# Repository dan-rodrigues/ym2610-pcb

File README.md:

# YM2610 PCB

This project allows the user to control a YM2610(B) FM synthesis / ADPCM / SSG sound chip. Software is included to play back YM2610(B) VGM files which includes any Neo Geo arcade game and various others. It can also play certain Sega Genesis tracks using an included converter script. There is also a MIDI input that can be paired with new software to control the synth.

The goal is to make the complete system both low-cost and flexible which increases the complexity of the FPGA design but allows the use of cheaper hardware (i.e. a $35USD FPGA board and a fairly straightforward PCB).

The FPGA board used is the [iCEBreaker Bitsy](https://1bitsquared.com/collections/fpga/products/icebreaker-bitsy) which is also [open source](https://github.com/icebreaker-fpga/icebreaker). It's the small purple board in the bottom left of the photo. A custom vendor USB device and a companion host Python script is used for control. The USB core used is [no2usb](https://github.com/no2fpga/no2usb).

## Assembled PCBs

### v1.1.0 (partial)

### v1.0.1

## Video/Audio demos

* [Metal Slug 2 soundtrack](https://www.youtube.com/watch?v=nlexW8DgMvw) - Neo Geo VGM playback demo using S/PDIF audio output.
* [Thunder Force IV soundtrack](https://www.youtube.com/watch?v=O-OgxfgEnMU) - Sega Genesis playback demo using analog line-out output.

The Sega Genesis demos are made using an included converter script to compensate for incompatible hardware, different clock rates and differences in PCM playback.

## Features

### I/O

* S/PDIF compatible outputs. The digital sound sources from the OPNB (FM/PCM) can be heard using this output. The analog sound source (SSG) can only be heard with the 3.5mm analog outputs. Optical and coax outputs are included.
* 3.5mm line out.
* 3.5mm headphone out with attenutation pot.
* Separate attenuation pots for the combined FM/PCM and separate SSG sound sources. Their levels can be adjusted or muted independently.
* MIDI input (DIN-5). Default firmware includes library functions to read the MIDI messages into a minimal struct. There's also a simple FM demo.
* 2x user buttons. The default firmware uses them to cycle through the available sound sources.

The S/PDIF output is resampled to 48KHz and can be used to hear the original lossless output from the OPNB. It doesn't include the analog SSG output but most tracks don't use it.

The analog outputs include an active low pass filter (fC = approx 17KHz), independent attenutation pots for each sound source and can also be used to hear the analog SSG output.

### Debug

These aren't required but can be useful for debugging.

* UART header
* CRESET jumper
* CRESET button

## Operation

Included is also an SoC implementation for the FPGA (in the `rtl/` directory) and firmware that runs on this SoC (in the `fw/` directory). There's also a set of helper scripts to control the SoC over the USB port.

ADPCM samples are fetched from the FPGA board PSRAM. The host PCB itself doesn't include any extra memory, only some standard logic to mux the PCM buses to the limited number of FPGA IO available. The RAM is 64MBit which is smaller than the 128MBit address space of samples, but the player script relocates and remaps samples starting from address 0 if needed. This means tracks that use the 128MBit space will work assuming the total PCM size of the track is less than 64MBit, which it likely is.

Both the original YM3016 DAC and the FPGA have access to the digital outputs of the synth. This means both analog output (using the DAC) and digital output (using the coax/optical output) is available. S/PDIF encoding is done on the FPGA and made available from the digital outputs.

The synth has a pair of PCM buses that work in parallel and the board only includes a single RAM which must be shared. The slower of the two buses is automatically paused when the faster bus begins a read which handles the contention issue. Only 4 FPGA IOs are used to read the 26 PCM bus pins which is handled using standard logic on the board.

The iCEBreaker Bitsy USB port is used to upload music data and also for control. The USB stack used and firmware can be customised as needed i.e. to allow a PC MIDI interface to drive the OPNB, or to record the raw digital output to store on a file, or any other possible use.

There is only 128KByte of RAM available to the software which would limit the maximum size of track that can be played. The track commands are streamed over USB to get around this limit which means tracks can be arbitrarily large. A pair of 8KByte buffers are read/written to support playback of large tracks.

Synth commands are output using a pair of 8bit shift registers, running at the same 8MHz clock as the synth itself. This reduces the needed IO count without being a bottleneck.

## Usage

### Build and flash

This project uses submodules which must be cloned first.

```
git submodule update --init --recursive
```

Building and flashing FPGA bitstream (which implements the SoC):

```
make dfuprog
```

Building and flashing SoC firmware:

```
make -C fw dfuprog
```

### Playing VGM files

After flashing the firmware, the RGB LED should slowly flash indicating that it's ready to use. Either `vgz` or `vgm` files can be used.

```
./scripts/usb_ctrl.py track.vgm
```

More details about the scripts can be found in their [README](scripts/README.md) file.

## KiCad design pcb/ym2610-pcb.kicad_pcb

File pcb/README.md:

# PCB

Included is the schematic and PCB layout of the board.

## Usage

Most ICs on the board are optional but a few are required in any case:

* 2x 74AHCT595: Shift registers to control the YM2610(B) and reset both the 2610 and the 3016.
* 1x 74LV1T34: Clock buffer, also shifts the 8MHz clock from 3.3v to 5v.

If ADPCM-A/B playback is needed, then these are required:

* 4x 74HCT153
* 1x 74LVC257
* 1x 74LVC2G08
* 1x 74LVC244

The analog section is optional assuming the SSG sound source isn't needed. To listen to the digital sound sources using S/PDIF output, there are optional optical and coax outputs. The coax output does not use a pulse transformer and one can be added if needed. 

## License

CERL-OHL-S-2.0. There is a copy of the text included in the licenses/ directory in the root of this repo. License text can also be found [here](https://ohwr.org/cern_ohl_s_v2.txt).

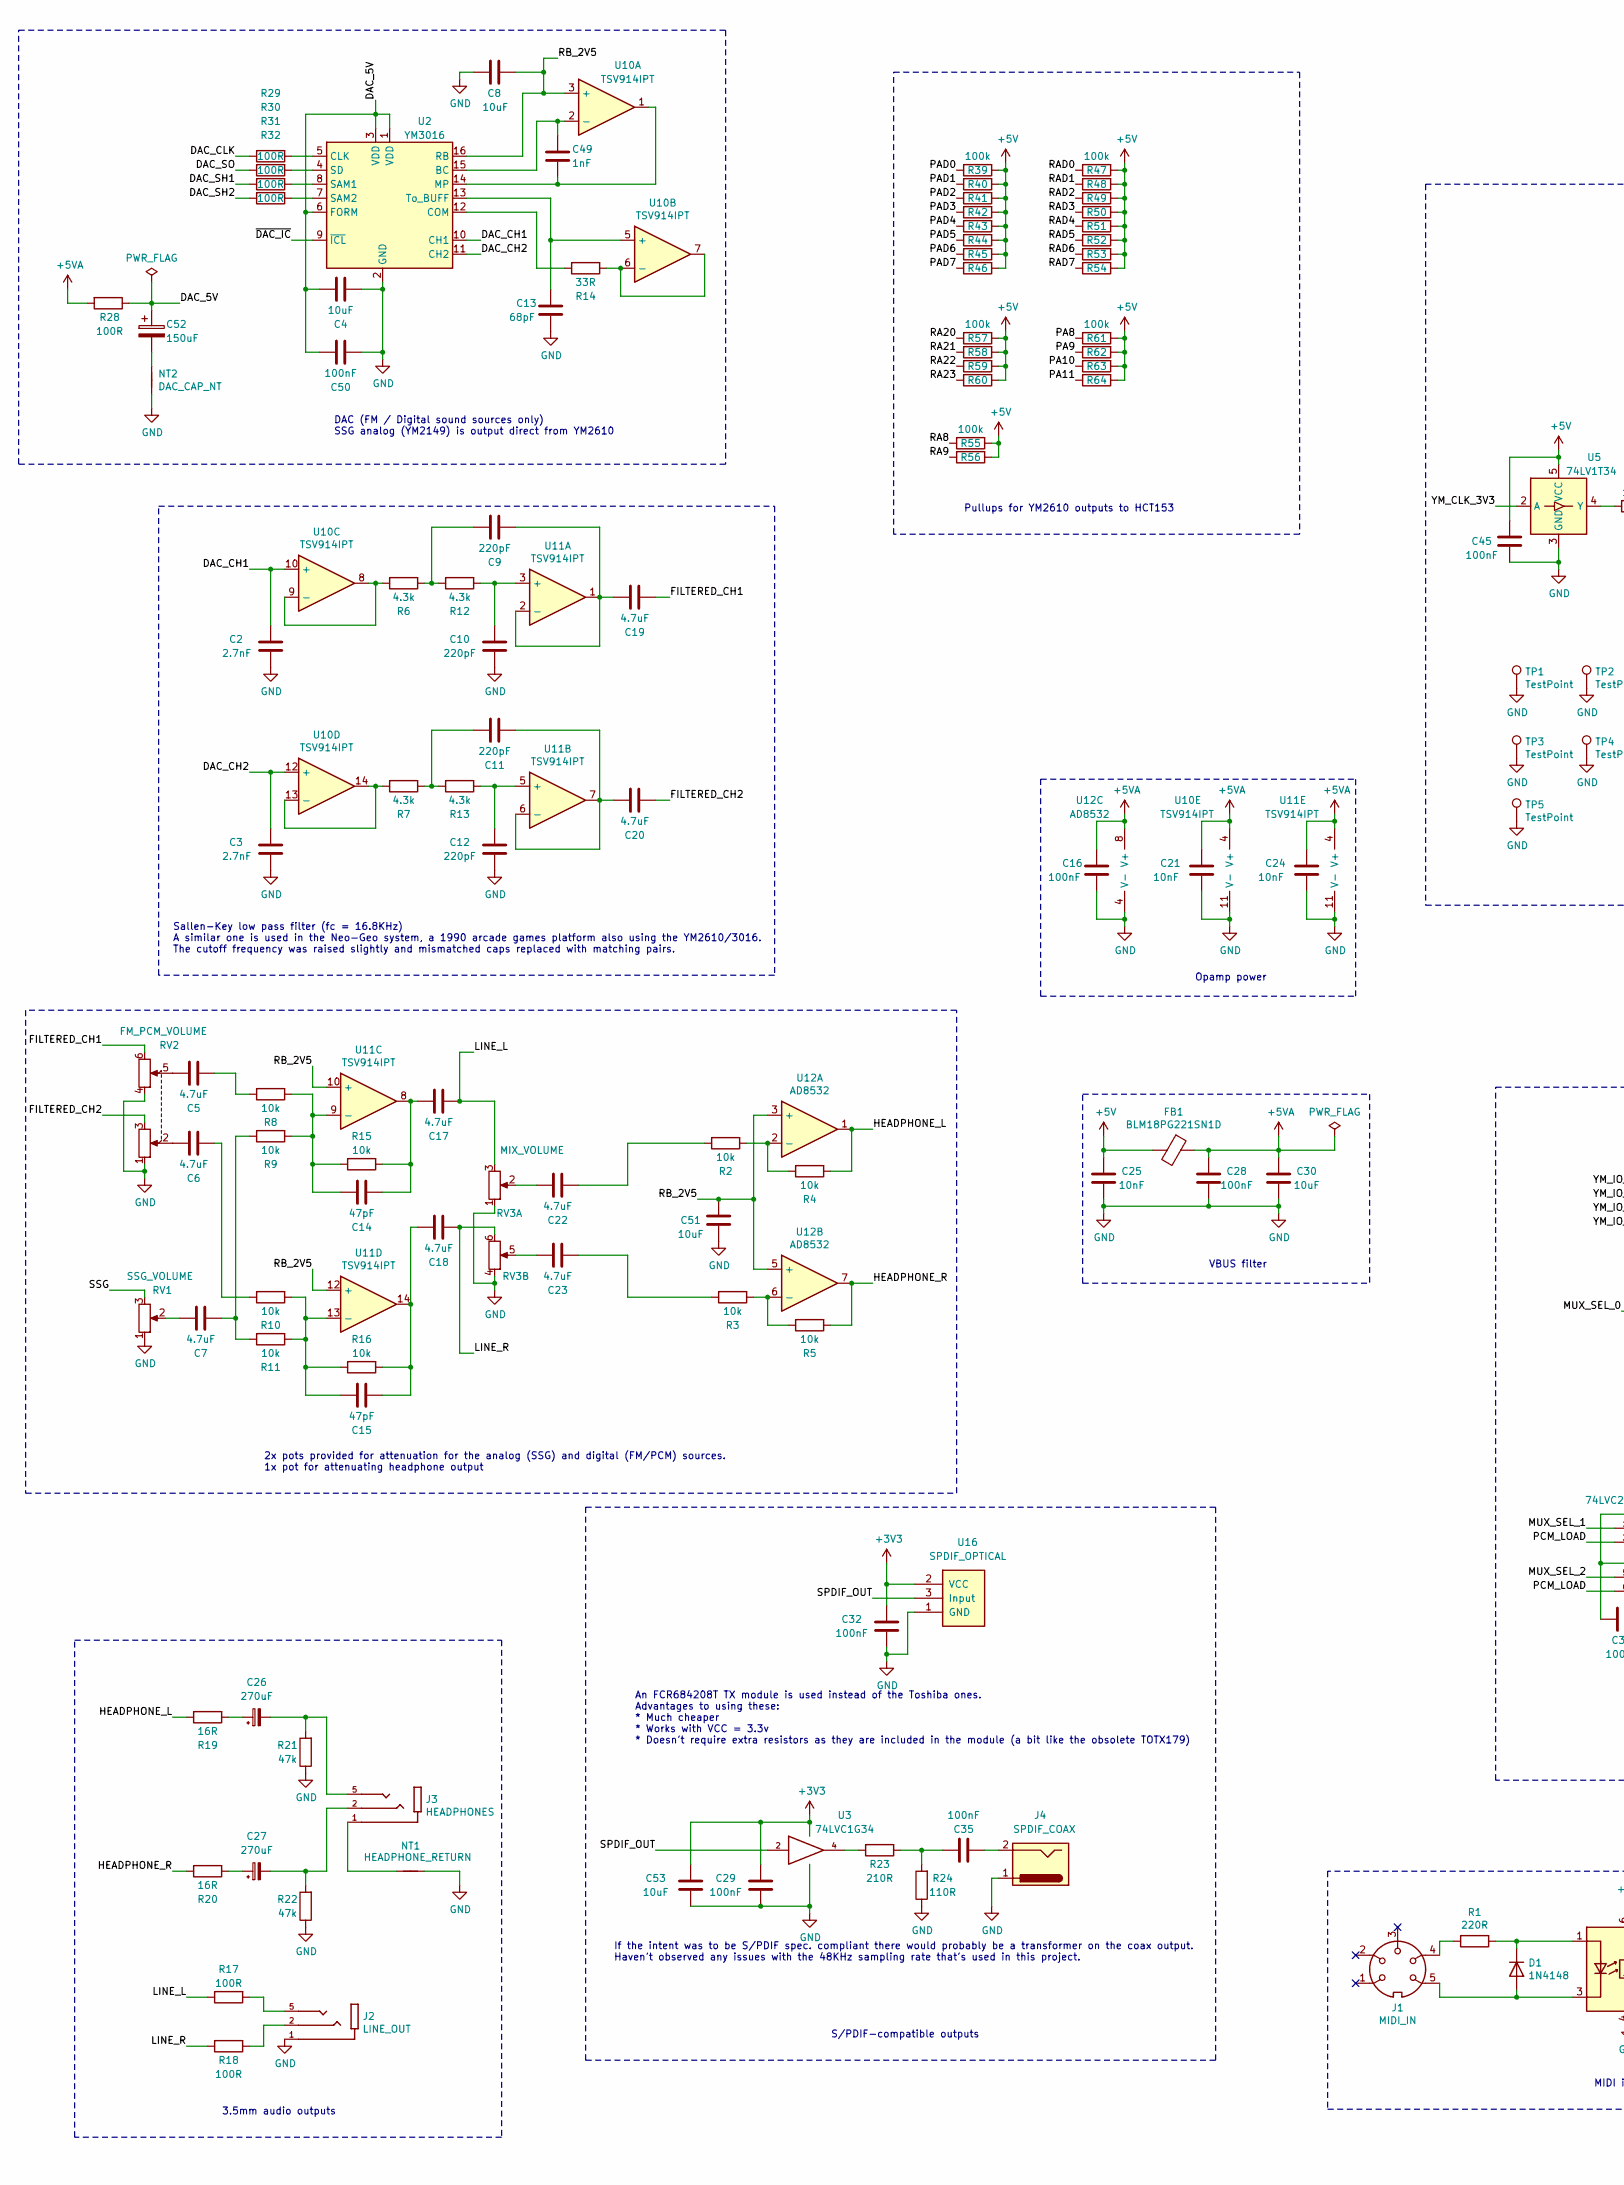
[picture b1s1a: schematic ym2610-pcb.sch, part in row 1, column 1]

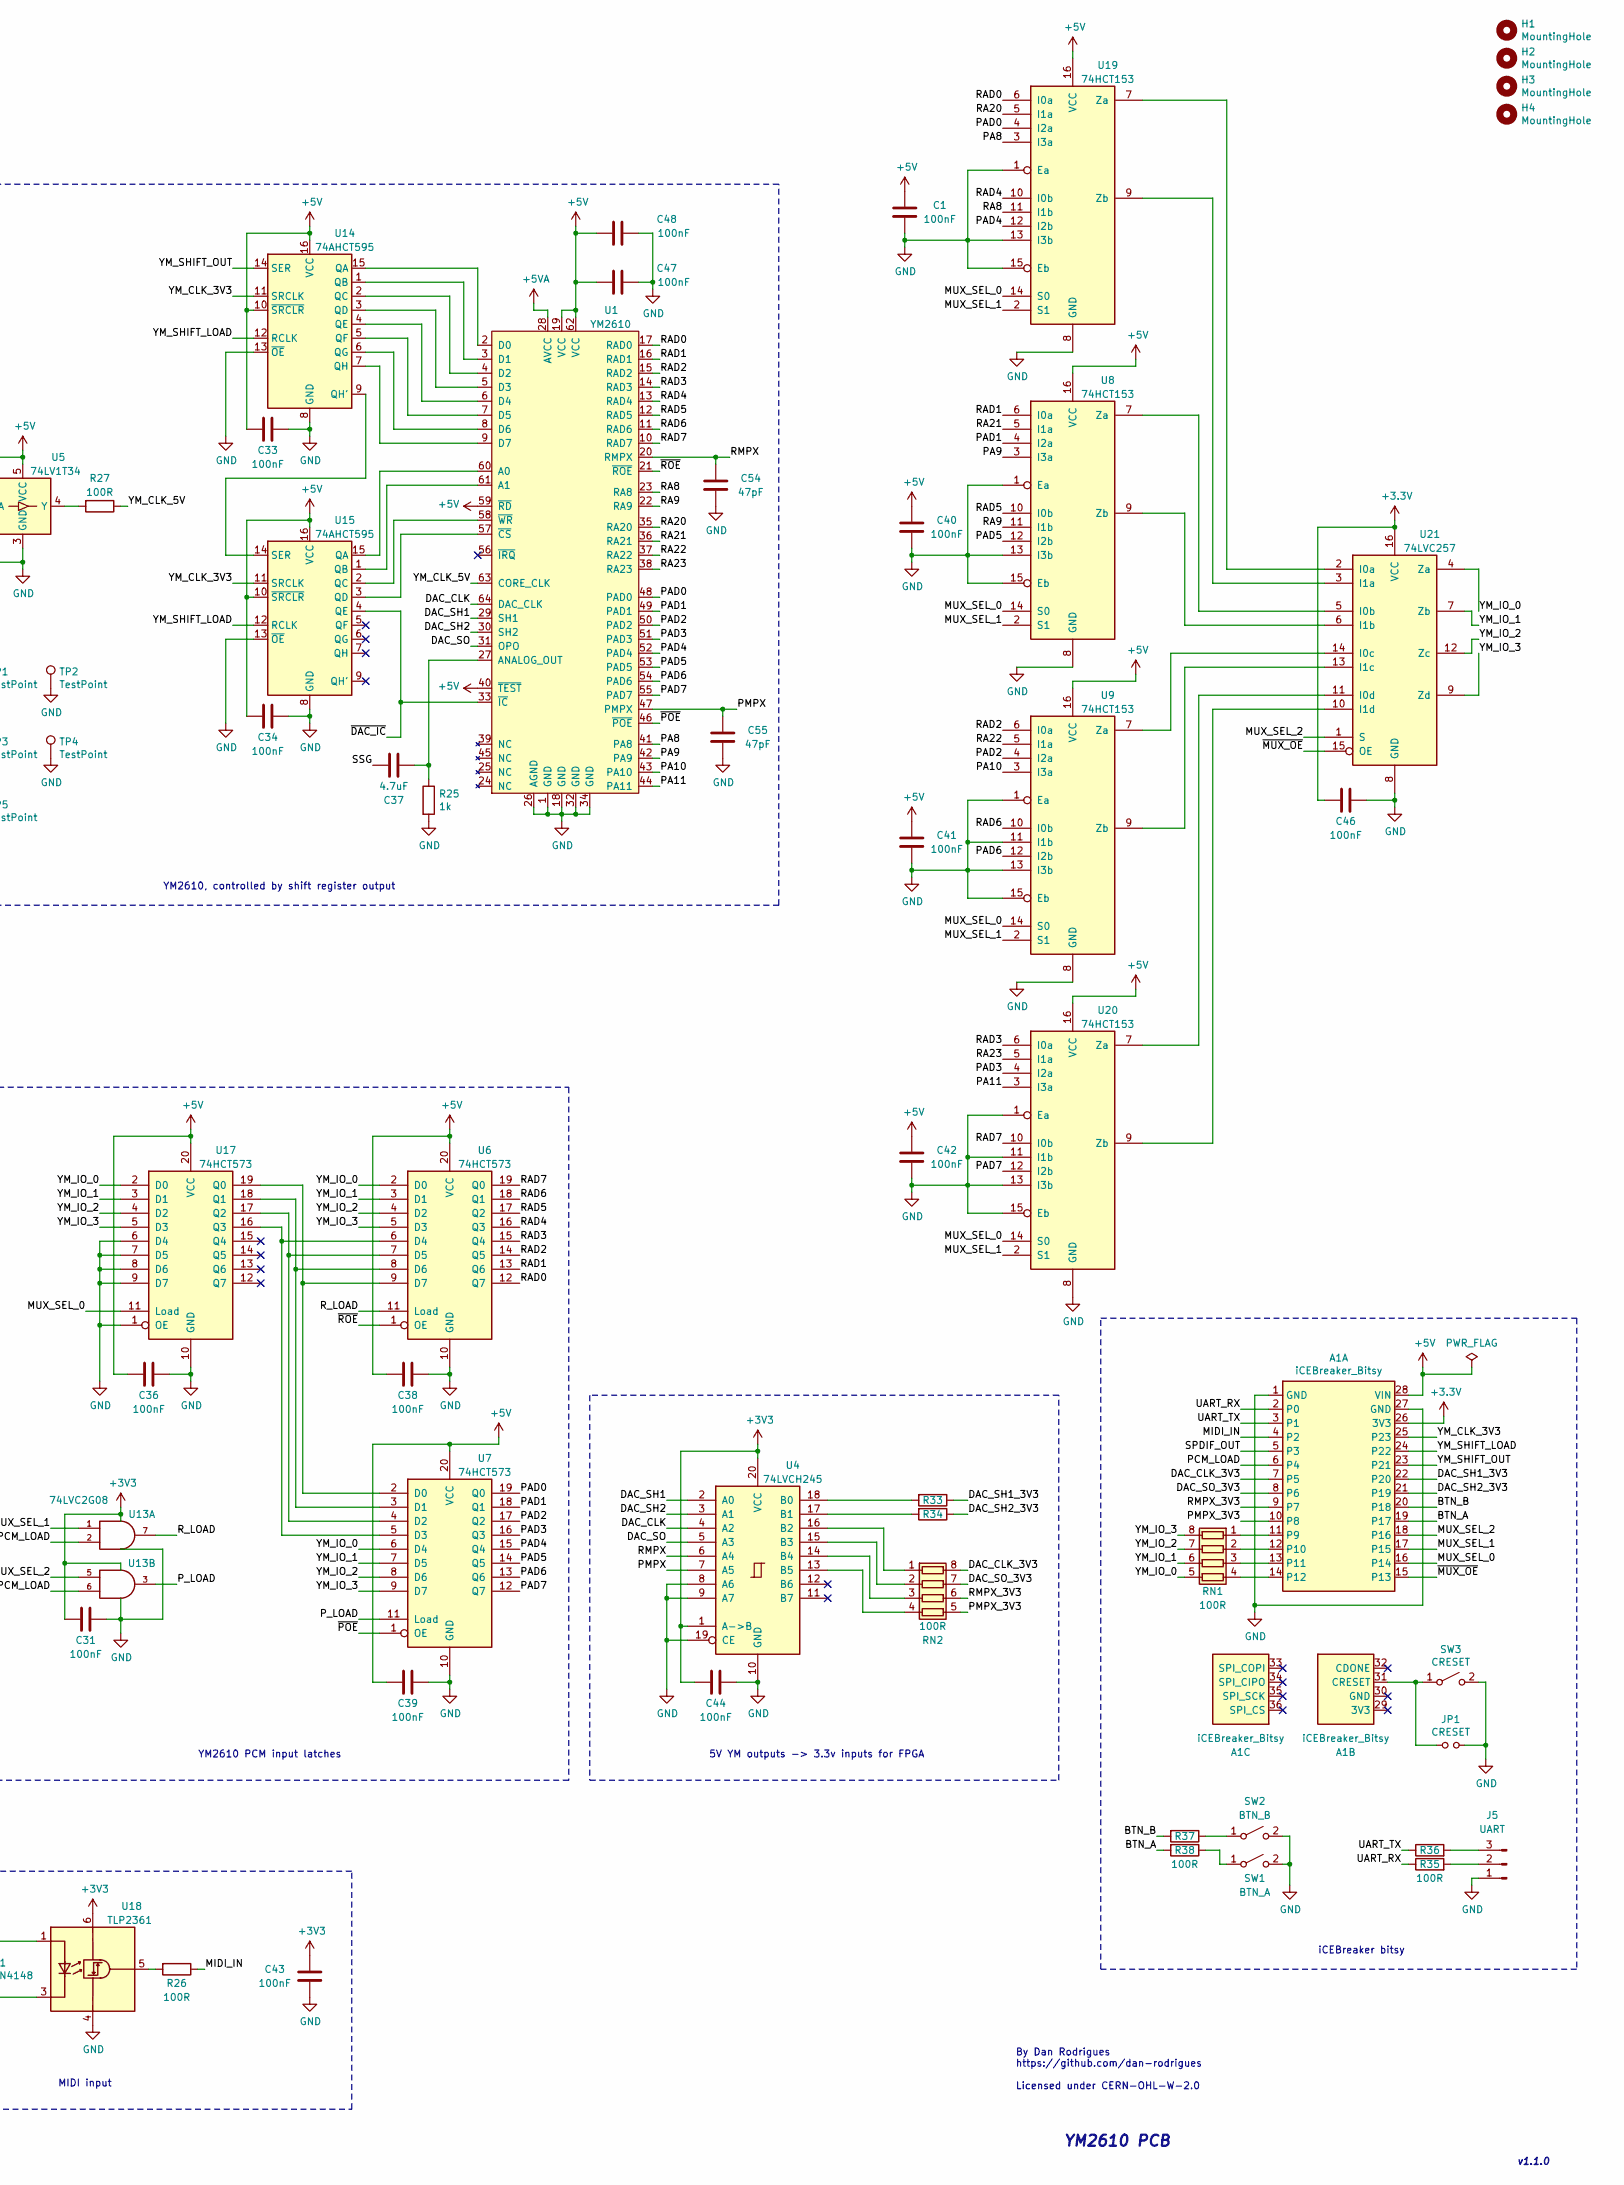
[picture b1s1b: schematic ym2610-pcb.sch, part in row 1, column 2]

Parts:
A1: iCEBreaker_Bitsy; iCEBreaker_Bitsy_THT
C1, C29, C31, C32, C33, C34, C35, C36, C38, C39, C40, C41, C42, C44, C45, C46, C47, C48: 100nF; C_0603_1608Metric
C2, C3: 2.7nF; C_0603_1608Metric; Voltage 10v
C4, C8, C30, C51: 10uF; C_0603_1608Metric; Voltage 10v
C5, C6, C7, C17, C18, C19, C20, C22, C23, C37: 4.7uF; C_0603_1608Metric; Voltage 10v
C9, C10, C11, C12: 220pF; C_0603_1608Metric; Voltage 10v
C13: 68pF; C_0603_1608Metric; Voltage 10v
C14, C15: 47pF; C_0603_1608Metric; Voltage 10v; Tolerance 5%
C16, C28, C50: 100nF; C_0603_1608Metric; Voltage 10v
C21, C24, C25: 10nF; C_0603_1608Metric; Voltage 10v
C26, C27: 270uF; CP_Elec_6.3x7.7; Voltage 10v
C43: 100nF; C_0603_1608Metric; Voltage 3.3v
C49: 1nF; C_0603_1608Metric; Voltage 10v
C52: 150uF; CP_Elec_5x5.8; Voltage 10v
C53: 10uF; C_0603_1608Metric
C54, C55: 47pF; C_0603_1608Metric
D1: 1N4148; D_SOD-323
FB1: BLM18PG221SN1D; L_0603_1608Metric
H1, H2, H3, H4: MountingHole; MountingHole_3.2mm_M3_DIN965
J1: MIDI_IN; CUI_SDS-50J
J2: LINE_OUT; SWITCHCRAFT_35RAPC2BH3; PARTREV J
J3: HEADPHONES; SWITCHCRAFT_35RAPC2BH3; PARTREV J
J4: SPDIF_COAX; RCJ-04
J5: UART; PinHeader_1x03_P2.54mm_Vertical
JP1: CRESET; PinHeader_1x02_P2.54mm_Vertical
NT1: HEADPHONE_RETURN; NetTie-2_SMD_Pad0.5mm
NT2: DAC_CAP_NT; NetTie-2_SMD_Pad0.5mm
R1: 220R; R_0603_1608Metric
R2, R3, R4, R5: 10k; R_0603_1608Metric
R6, R7, R12, R13: 4.3k; R_0603_1608Metric; Tolerance 1%
R8, R9, R10, R11, R15, R16: 10k; R_0603_1608Metric; Tolerance 1%
R14: 33R; R_0603_1608Metric; Tolerance 1%
R17, R18, R26, R27, R28, R29, R30, R31, R32, R33, R34, R35, R36, R37, R38: 100R; R_0603_1608Metric
R19, R20: 16R; R_0603_1608Metric
R21, R22: 47k; R_0603_1608Metric
R23: 210R; R_0603_1608Metric
R24: 110R; R_0603_1608Metric
R25: 1k; R_0603_1608Metric; Tolerance 1%
R39, R40, R41, R42, R43, R44, R45, R46, R47, R48, R49, R50, R51, R52, R53, R54, R55, R56, R57, R58, R59, R60, R61, R62, R63, R64: 100k; R_0603_1608Metric
RN1, RN2: 100R; R_Array_Convex_4x0603
RV1: SSG_VOLUME; PTD901-2015K-A103
RV2: FM_PCM_VOLUME; PTD902-2020K-A103
RV3: MIX_VOLUME; PTD902-2020K-A103
SW1: BTN_A; SW_SPST_PTS645
SW2: BTN_B; SW_SPST_PTS645
SW3: CRESET; SW_SPST_PTS645
TP1, TP2, TP3, TP4, TP5: TestPoint; TestPoint_Pad_D1.0mm
U1: YM2610; DIP-64_W19.05mm_P1.78mm_Socket
U2: YM3016; DIP-16_W7.62mm_Socket
U3: 74LVC1G34; SOT-353_SC-70-5
U4: 74LVCH245; TSSOP-20_4.4x6.5mm_P0.65mm
U5: 74LV1T34; SOT-23-5
U6, U7, U17: 74HCT573; TSSOP-20_4.4x6.5mm_P0.65mm
U8, U9, U19, U20: 74HCT153; TSSOP-16_4.4x5mm_P0.65mm
U10, U11: TSV914IPT; TSSOP-14_4.4x5mm_P0.65mm
U12: AD8532; TSSOP-8_4.4x3mm_P0.65mm
U13: 74LVC2G08; TSSOP-8_3x3mm_P0.65mm
U14, U15: 74AHCT595; TSSOP-16_4.4x5mm_P0.65mm
U16: SPDIF_OPTICAL; FCR684208T
U18: TLP2361; SOIC-6-5_W4.55mm
U21: 74LVC257; TSSOP-16_4.4x5mm_P0.65mm

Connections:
+5V: A1.28 (VIN), C1.2, C25.1, C33.2, C34.2, C36.1, C38.2, C39.2, C40.2, C41.2, C42.2, C45.2, C47.2, C48.2, FB1.2, R39.1, R40.1, R41.1, R42.1, R43.1, R44.1, R45.1, R46.1, R47.1, R48.1, R49.1, R50.1, R51.1, R52.1, R53.1, R54.1, R55.1, R56.1, R57.1, R58.1, R59.1, R60.1, R61.1, R62.1, R63.1, R64.1, U1.19 (VCC), U1.40 (~TEST), U1.59 (~RD), U1.62 (VCC), U5.5 (VCC), U6.20 (VCC), U7.20 (VCC), U8.16 (VCC), U9.16 (VCC), U14.10 (~SRCLR), U14.16 (VCC), U15.10 (~SRCLR), U15.16 (VCC), U17.20 (VCC), U19.16 (VCC), U20.16 (VCC)
+5VA: C16.1, C21.1, C24.1, C28.1, C30.1, FB1.1, R28.2, U1.28 (AVCC), U10.4 (V+), U11.4 (V+), U12.8 (V+)
/BTN_A: A1.19 (P17), R38.2
/BTN_B: A1.20 (P18), R37.2
/DAC_5V: C4.2, C50.2, C52.1, R28.1, U2.1 (VDD), U2.3 (VDD), U2.6 (FORM)
/DAC_CH1: C2.1, U2.10 (CH1), U10.10 (+)
/DAC_CH2: C3.1, U2.11 (CH2), U10.12 (+)
/DAC_CLK: R29.2, U1.64 (DAC_CLK), U4.4 (A2)
/DAC_CLK_3V3: A1.7 (P5), RN2.8 (R1.2)
/DAC_SH1: R31.2, U1.29 (SH1), U4.2 (A0)
/DAC_SH1_3V3: A1.22 (P20), R33.1
/DAC_SH2: R32.2, U1.30 (SH2), U4.3 (A1)
/DAC_SH2_3V3: A1.21 (P19), R34.1
/DAC_SO: R30.2, U1.31 (OPO), U4.5 (A3)
/DAC_SO_3V3: A1.8 (P6), RN2.7 (R2.2)
/FILTERED_CH1: C19.1, RV2.6
/FILTERED_CH2: C20.1, RV2.3
/HEADPHONE_L: R4.1, R19.2, U12.1
/HEADPHONE_R: R5.1, R20.2, U12.7
/LINE_L: C17.1, R17.2, RV3.3
/LINE_R: C18.1, R18.2, RV3.6
/MIDI_IN: A1.4 (P2), R26.1
/MUX_SEL_0: A1.16 (P14), U8.14 (S0), U9.14 (S0), U17.11 (Load), U19.14 (S0), U20.14 (S0)
/MUX_SEL_1: A1.17 (P15), U8.2 (S1), U9.2 (S1), U13.1, U19.2 (S1), U20.2 (S1)
/MUX_SEL_2: A1.18 (P16), U13.5, U21.1 (S)
/PA8: R61.2, U1.41 (PA8), U19.3 (I3a)
/PA9: R62.2, U1.42 (PA9), U8.3 (I3a)
/PA10: R63.2, U1.43 (PA10), U9.3 (I3a)
/PA11: R64.2, U1.44 (PA11), U20.3 (I3a)
/PAD0: R39.2, U1.48 (PAD0), U7.19 (Q0), U19.4 (I2a)
/PAD1: R40.2, U1.49 (PAD1), U7.18 (Q1), U8.4 (I2a)
/PAD2: R41.2, U1.50 (PAD2), U7.17 (Q2), U9.4 (I2a)
/PAD3: R42.2, U1.51 (PAD3), U7.16 (Q3), U20.4 (I2a)
/PAD4: R43.2, U1.52 (PAD4), U7.15 (Q4), U19.12 (I2b)
/PAD5: R44.2, U1.53 (PAD5), U7.14 (Q5), U8.12 (I2b)
/PAD6: R45.2, U1.54 (PAD6), U7.13 (Q6), U9.12 (I2b)
/PAD7: R46.2, U1.55 (PAD7), U7.12 (Q7), U20.12 (I2b)
/PCM_LOAD: A1.6 (P4), U13.2, U13.6
/PMPX: C55.2, U1.47 (PMPX), U4.7 (A5)
/PMPX_3V3: A1.10 (P8), RN2.5 (R4.2)
/P_LOAD: U7.11 (Load), U13.3
/RA8: R55.2, U1.23 (RA8), U19.11 (I1b)
/RA9: R56.2, U1.22 (RA9), U8.11 (I1b)
/RA20: R57.2, U1.35 (RA20), U19.5 (I1a)
/RA21: R58.2, U1.36 (RA21), U8.5 (I1a)
/RA22: R59.2, U1.37 (RA22), U9.5 (I1a)
/RA23: R60.2, U1.38 (RA23), U20.5 (I1a)
/RAD0: R47.2, U1.17 (RAD0), U6.12 (Q7), U19.6 (I0a)
/RAD1: R48.2, U1.16 (RAD1), U6.13 (Q6), U8.6 (I0a)
/RAD2: R49.2, U1.15 (RAD2), U6.14 (Q5), U9.6 (I0a)
/RAD3: R50.2, U1.14 (RAD3), U6.15 (Q4), U20.6 (I0a)
/RAD4: R51.2, U1.13 (RAD4), U6.16 (Q3), U19.10 (I0b)
/RAD5: R52.2, U1.12 (RAD5), U6.17 (Q2), U8.10 (I0b)
/RAD6: R53.2, U1.11 (RAD6), U6.18 (Q1), U9.10 (I0b)
/RAD7: R54.2, U1.10 (RAD7), U6.19 (Q0), U20.10 (I0b)
/RB_2V5: C8.1, C51.2, U2.16 (RB), U10.3 (+), U11.10 (+), U11.12 (+), U12.3 (+), U12.5 (+)
/RMPX: C54.2, U1.20 (RMPX), U4.6 (A4)
/RMPX_3V3: A1.9 (P7), RN2.6 (R3.2)
/R_LOAD: U6.11 (Load), U13.7
/SPDIF_OUT: A1.5 (P3), U3.2, U16.3 (Input)
/SSG: C37.2, RV1.3
/UART_RX: A1.2 (P0), R35.1
/UART_TX: A1.3 (P1), R36.1
/YM_CLK_3V3: A1.25 (P23), U5.2 (A), U14.11 (SRCLK), U15.11 (SRCLK)
/YM_CLK_5V: R27.1, U1.63 (CORE_CLK)
/YM_IO_0: RN1.5 (R4.2), U6.2 (D0), U7.6 (D4), U17.2 (D0), U21.4 (Za)
/YM_IO_1: RN1.6 (R3.2), U6.3 (D1), U7.7 (D5), U17.3 (D1), U21.7 (Zb)
/YM_IO_2: RN1.7 (R2.2), U6.4 (D2), U7.8 (D6), U17.4 (D2), U21.12 (Zc)
/YM_IO_3: RN1.8 (R1.2), U6.5 (D3), U7.9 (D7), U17.5 (D3), U21.9 (Zd)
/YM_SHIFT_LOAD: A1.24 (P22), U14.12 (RCLK), U15.12 (RCLK)
/YM_SHIFT_OUT: A1.23 (P21), U14.14 (SER)
/~DAC_IC: U1.33 (~IC), U2.9 (~ICL), U15.4 (QE)
/~MUX_OE: A1.15 (P13), U21.15 (OE)
/~POE: U1.46 (~POE), U7.1 (OE)
/~ROE: U1.21 (~ROE), U6.1 (OE)
GND: A1.1 (GND), A1.27 (GND), C1.1, C2.2, C3.2, C4.1, C8.2, C10.1, C12.1, C13.2, C16.2, C21.2, C24.2, C25.2, C28.2, C29.1, C30.2, C31.2, C32.1, C33.1, C34.1, C36.2, C38.1, C39.1, C40.1, C41.1, C42.1, C43.1, C44.1, C45.1, C46.1, C47.1, C48.1, C50.1, C51.1, C53.1, C54.1, C55.1, J2.1, J4.1, J5.1, JP1.2, NT1.2, NT2.2, R21.1, R22.1, R24.1, R25.2, RV1.1, RV2.1, RV2.4, RV3.1, RV3.4, SW1.2 (B), SW2.2 (B), SW3.2 (B), TP1.1, TP2.1, TP3.1, TP4.1, TP5.1, U1.1 (GND), U1.18 (GND), U1.26 (AGND), U1.32 (GND), U1.34 (GND), U2.2 (GND), U3.3 (GND), U4.8 (A6), U4.9 (A7), U4.10 (GND), U4.19 (CE), U5.3 (GND), U6.10 (GND), U7.10 (GND), U8.1 (Ea), U8.8 (GND), U8.13 (I3b), U8.15 (Eb), U9.1 (Ea), U9.8 (GND), U9.11 (I1b), U9.13 (I3b), U9.15 (Eb), U10.11 (V-), U11.11 (V-), U12.4 (V-), U13.4 (GND), U14.8 (GND), U14.13 (~OE), U15.8 (GND), U15.13 (~OE), U16.1 (GND), U17.1 (OE), U17.6 (D4), U17.7 (D5), U17.8 (D6), U17.9 (D7), U17.10 (GND), U18.4 (GND), U19.1 (Ea), U19.8 (GND), U19.13 (I3b), U19.15 (Eb), U20.1 (Ea), U20.8 (GND), U20.11 (I1b), U20.13 (I3b), U20.15 (Eb), U21.8 (GND)
unnamed: A1.11 (P9), RN1.1 (R1.1)
unnamed: A1.12 (P10), RN1.2 (R2.1)
unnamed: A1.13 (P11), RN1.3 (R3.1)
unnamed: A1.14 (P12), RN1.4 (R4.1)
unnamed: A1.31 (CRESET), JP1.1, SW3.1 (A)
unnamed: C5.1, R8.2
unnamed: C5.2, RV2.5
unnamed: C6.1, R10.2
unnamed: C6.2, RV2.2
unnamed: C7.1, R9.2, R11.2
unnamed: C7.2, RV1.2
unnamed: C9.2, R6.1, R12.2
unnamed: C10.2, R12.1, U11.3 (+)
unnamed: C11.1, C20.2, U11.6 (-), U11.7
unnamed: C11.2, R7.1, R13.2
unnamed: C12.2, R13.1, U11.5 (+)
unnamed: C13.1, U2.13 (To_BUFF), U10.5 (+)
unnamed: C14.1, C17.2, R15.1, U11.8
unnamed: C14.2, R8.1, R9.1, R15.2, U11.9 (-)
unnamed: C15.1, C18.2, R16.1, U11.14
unnamed: C15.2, R10.1, R11.1, R16.2, U11.13 (-)
unnamed: C9.1, C19.2, U11.1, U11.2 (-)
unnamed: C22.1, R2.2
unnamed: C22.2, RV3.2
unnamed: C23.1, R3.2
unnamed: C23.2, RV3.5
unnamed: C26.1, R19.1
unnamed: C26.2, J3.5, R21.2
unnamed: C27.1, R20.1
unnamed: C27.2, J3.2, R22.2
unnamed: C35.1, J4.2
unnamed: C35.2, R23.1, R24.2
unnamed: C37.1, R25.1, U1.27 (ANALOG_OUT)
unnamed: C49.1, U2.14 (MP), U10.1
unnamed: C49.2, U2.15 (BC), U10.2 (-)
unnamed: C52.2, NT2.1
unnamed: D1.1 (K), R1.1, U18.1 (A)
unnamed: D1.2 (A), J1.5, U18.3 (K)
unnamed: J1.4, R1.2
unnamed: J2.2, R18.1
unnamed: J2.5, R17.1
unnamed: J3.1, NT1.1
unnamed: J5.2, R35.2
unnamed: J5.3, R36.2
unnamed: R2.1, R4.2, U12.2 (-)
unnamed: R3.1, R5.2, U12.6 (-)
unnamed: R6.2, U10.8, U10.9 (-)
unnamed: R7.2, U10.13 (-), U10.14
unnamed: R14.1, U10.6 (-), U10.7
unnamed: R14.2, U2.12 (COM)
unnamed: R23.2, U3.4
unnamed: R26.2, U18.5 (VO)
unnamed: R27.2, U5.4 (Y)
unnamed: R29.1, U2.5 (CLK)
unnamed: R30.1, U2.4 (SD)
unnamed: R31.1, U2.8 (SAM1)
unnamed: R32.1, U2.7 (SAM2)
unnamed: R33.2, U4.18 (B0)
unnamed: R34.2, U4.17 (B1)
unnamed: R37.1, SW2.1 (A)
unnamed: R38.1, SW1.1 (A)
unnamed: RN2.1 (R1.1), U4.16 (B2)
unnamed: RN2.2 (R2.1), U4.15 (B3)
unnamed: RN2.3 (R3.1), U4.14 (B4)
unnamed: RN2.4 (R4.1), U4.13 (B5)
unnamed: U1.2 (D0), U14.15 (QA)
unnamed: U1.3 (D1), U14.1 (QB)
unnamed: U1.4 (D2), U14.2 (QC)
unnamed: U1.5 (D3), U14.3 (QD)
unnamed: U1.6 (D4), U14.4 (QE)
unnamed: U1.7 (D5), U14.5 (QF)
unnamed: U1.8 (D6), U14.6 (QG)
unnamed: U1.9 (D7), U14.7 (QH)
unnamed: U1.57 (~CS), U15.3 (QD)
unnamed: U1.58 (~WR), U15.2 (QC)
unnamed: U1.60 (A0), U15.15 (QA)
unnamed: U1.61 (A1), U15.1 (QB)
unnamed: U14.9 (QH'), U15.14 (SER)
unnamed: U6.6 (D4), U7.5 (D3), U17.16 (Q3)
unnamed: U6.7 (D5), U7.4 (D2), U17.17 (Q2)
unnamed: U6.8 (D6), U7.3 (D1), U17.18 (Q1)
unnamed: U6.9 (D7), U7.2 (D0), U17.19 (Q0)
unnamed: U19.7 (Za), U21.2 (I0a)
unnamed: U19.9 (Zb), U21.3 (I1a)
unnamed: U20.7 (Za), U21.11 (I0d)
unnamed: U20.9 (Zb), U21.10 (I1d)
unnamed: U8.7 (Za), U21.5 (I0b)
unnamed: U8.9 (Zb), U21.6 (I1b)
unnamed: U9.9 (Zb), U21.13 (I1c)
unnamed: U9.7 (Za), U21.14 (I0c)

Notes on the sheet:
Sallen-Key low pass filter (fc = 16.8KHz) A similar one is used in the Neo-Geo system, a 1990 arcade games platform also using the YM2610/3016. The cutoff frequency was raised slightly and mismatched caps replaced with matching pairs.
VBUS filter
2x pots provided for attenuation for the analog (SSG) and digital (FM/PCM) sources. 1x pot for attenuating headphone output
If the intent was to be S/PDIF spec. compliant there would probably be a transformer on the coax output. Haven’t observed any issues with the 48KHz sampling rate that’s used in this project.
An FCR684208T TX module is used instead of the Toshiba ones. Advantages to using these: * Much cheaper * Works with VCC = 3.3v * Doesn’t require extra resistors as they are included in the module (a bit like the obsolete TOTX179)
3.5mm audio outputs
S/PDIF-compatible outputs
MIDI input
Pullups for YM2610 outputs to HCT153
DAC (FM / Digital sound sources only) SSG analog (YM2149) is output direct from YM2610
YM2610 PCM input latches
YM2610, controlled by shift register output
5V YM outputs -> 3.3v inputs for FPGA
iCEBreaker bitsy
Opamp power
YM2610 PCB
v1.1.0
By Dan Rodrigues https://github.com/dan-rodrigues Licensed under CERN-OHL-W-2.0

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
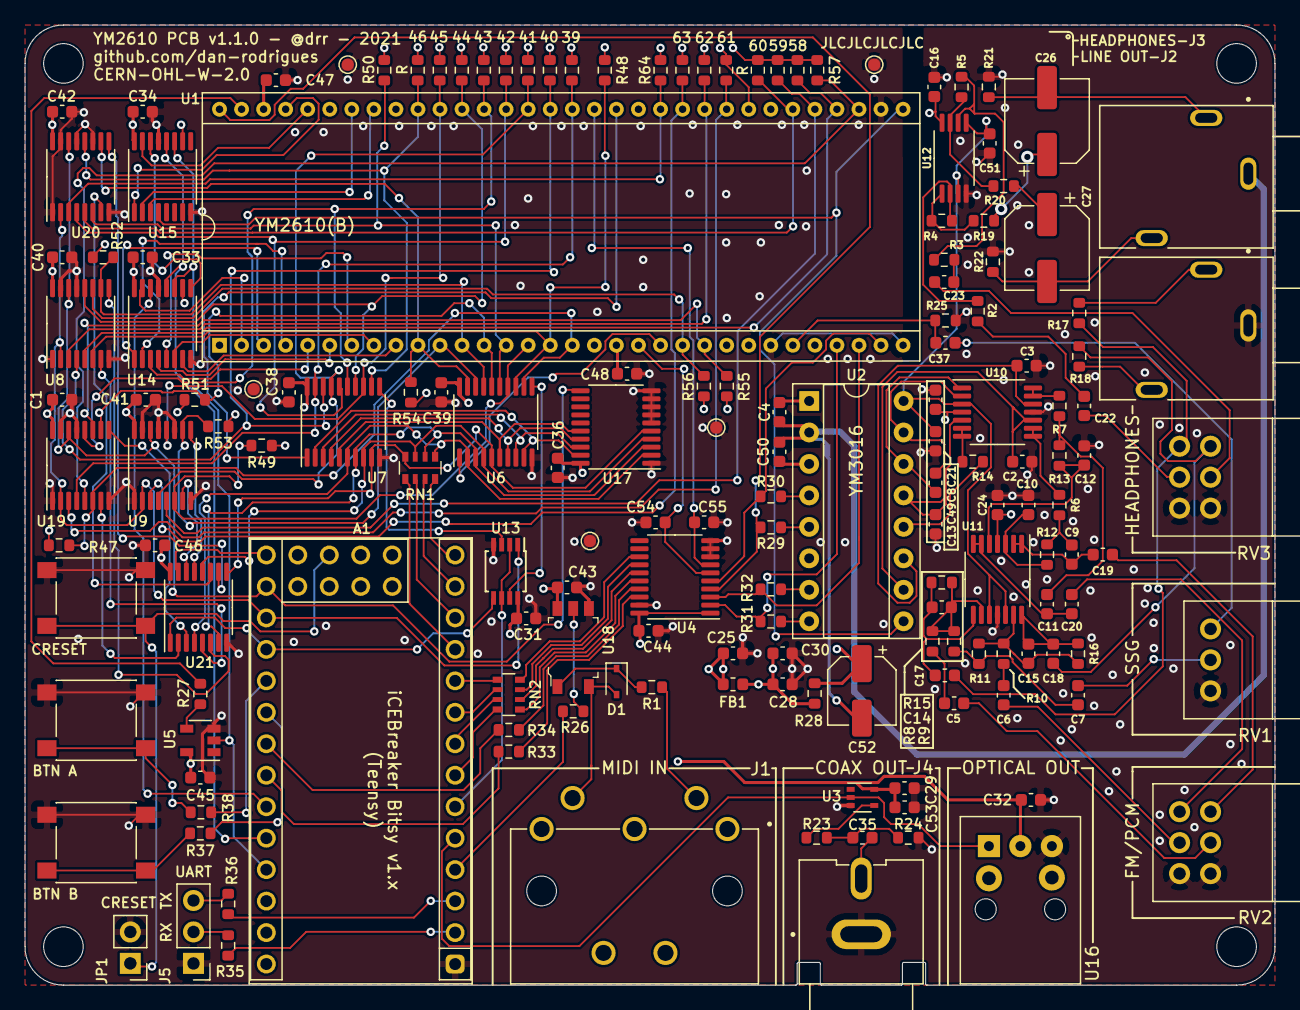
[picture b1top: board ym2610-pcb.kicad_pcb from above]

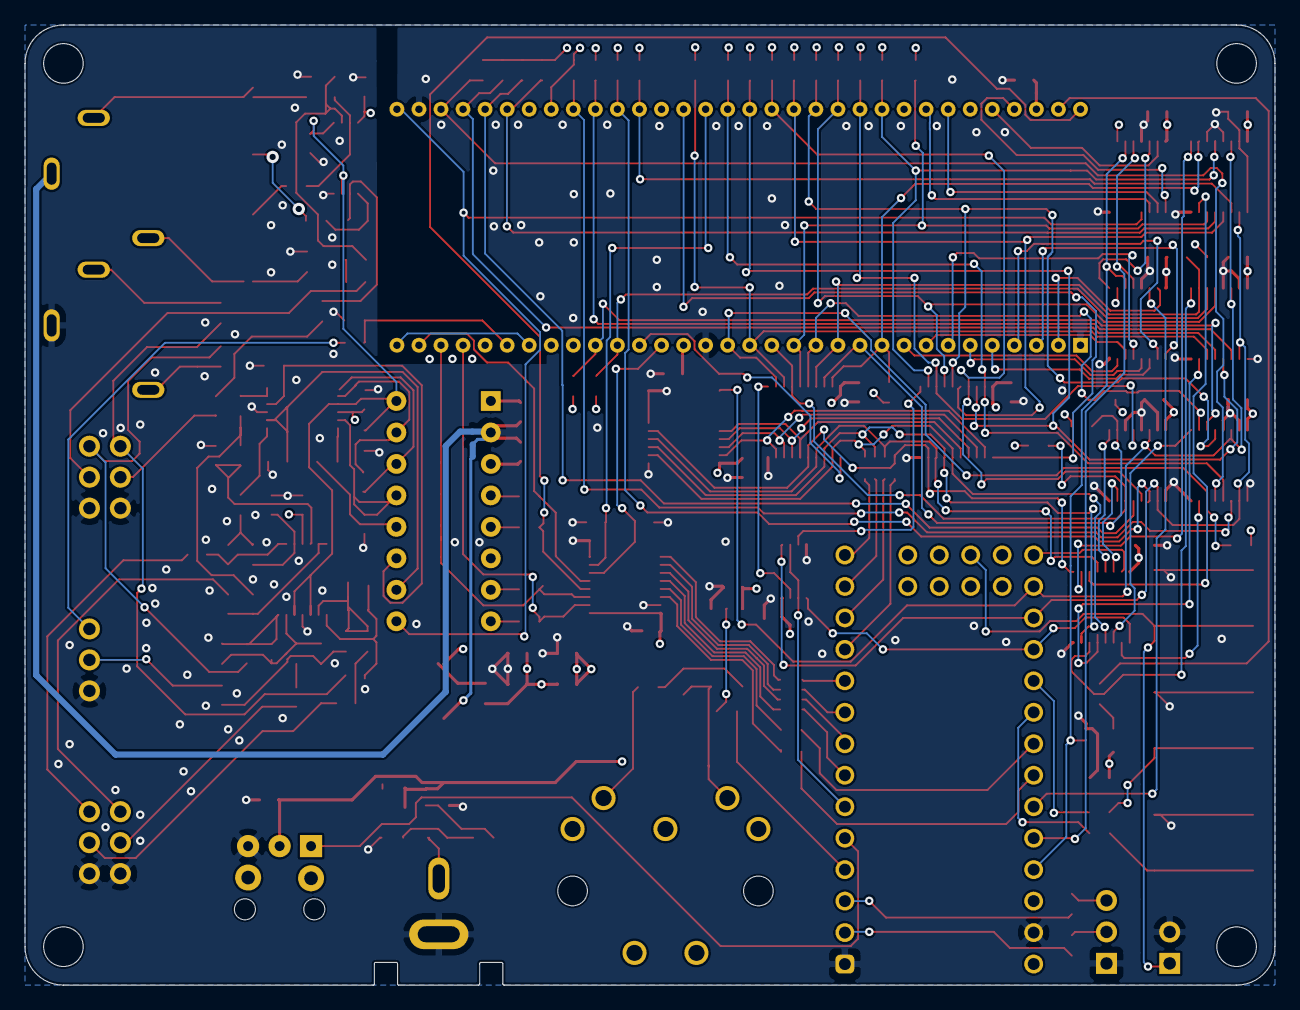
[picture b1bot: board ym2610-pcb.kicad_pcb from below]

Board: 4 copper layers, 100.9 x 77.5 mm, 168 parts (2 on the bottom side), 167 nets.

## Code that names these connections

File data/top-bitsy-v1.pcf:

# YM2610 PCM Mux (discrete logic)

set_io ym_io[0] 20
set_io ym_io[1] 13
set_io ym_io[2] 21
set_io ym_io[3] 12

set_io mux_sel[0] 23
set_io mux_sel[1] 27
set_io mux_sel[2] 26

set_io mux_oe_n 25
set_io pcm_load 4
set_io rmpx 10
set_io pmpx 11

# YM3016

set_io dac_clk 3
set_io dac_sh1 34
set_io dac_sh2 32
set_io dac_so 9

# SPDIF

set_io spdif_out 45

# MIDI

set_io midi_rx 48

# SPI
set_io spi_io[0] 14
set_io spi_io[1] 17
set_io spi_io[2] 18
set_io spi_io[3] 19

set_io -nowarn spi_clk 15
set_io -nowarn spi_flash_cs_n 16
set_io -nowarn spi_ram_cs_n 6

# USB
set_io -nowarn usb_dp 42
set_io -nowarn usb_dn 38
set_io -nowarn usb_pu 37

# UART
set_io -nowarn uart_rx 47
set_io -nowarn uart_tx 44

# Clock
set_io -nowarn clk_in 35

# Button (bitsy)
set_io -nowarn btn 2

# Button (PCB)
set_io -pullup yes -pullup_resistor 3P3K btn_a 28
set_io -pullup yes -pullup_resistor 3P3K btn_b 31
 
# Leds
set_io -nowarn rgb[0] 39
set_io -nowarn rgb[1] 40
set_io -nowarn rgb[2] 41

# Both an IO + LED on 24?
#set_io led 25

# YM2610

set_io ym_clk 46
set_io ym_shift_load 43
set_io ym_shift_out 36

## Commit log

2021-03-07 Restore repo
2021-03-07 util: remove now-unused header generator
2021-03-07 doc: add partially assembled, but working, PCB photo
2021-03-08 hw/sw: add YM2610 command FIFO and hardware timer for delays
2021-03-08 pcb: bump version from v1.0.0 to tentative v1.0.1a
2021-03-10 hw/sw: extend reset pulse (min 192 cycles @ 8MHz)
2021-03-10 pcb: replace LV1T34 with LVC1G34 as S/PDIF coax buffer
    The earlier design used the LVC part but to remove a unique item from BOM, it was replaced with another LV1 part. This was a mistake as the LV1T34 can't quite drive the coax load (vs. 24mA on the LVC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
2021-03-11 rtl/sw/util: various bits of cleanup and groundwork for command streaming
2021-03-13 sw/util: extra support for double buffered vgm streaming
2021-03-13 rtl: ADPCMB fetch optimization
2021-03-13 util: minor USB script cleanup
2021-03-14 sw: initial MIDI input support
2021-03-14 Minor comment changes
2021-03-15 sw/rtl: add 2 extra PCB buttons and FM/PCM control
2021-03-16 sw: various optimizations
2021-03-17 sw: support per-channel FM masking (for MIDI)
2021-03-17 sw: add build-time filtering for FM
2021-03-17 sw: rever to enabling all FM channels by default
2021-03-19 rtl: minor cleanup
2021-03-19 rtl: more minor cleanup
2021-03-19 rtl: eliminate a few unnecessary resets
2021-03-20 rtl / sw: fix ADPCM-B playback glitch
2021-03-20 rtl: default to debug regs being disabled
    Speeds up synth + PAR
2021-03-20 sw: cleanup regs access using more structs
2021-03-20 misc: clarified licenses
2021-03-20 sw / util: clean up in preparation for YM2612
2021-03-20 sw / rtl: revised timer setup for accuracy
    New approach uses a timer that always keeps decrementing rather than suspending when timer expires
2021-03-20 sw: reg access cleanup
2021-03-20 sw: move playback-start code before continue-playback code
2021-03-20 sw: allow timer to be reset to zero now
2021-03-21 doc: update README and photo or partial assembly
2021-03-21 pcb: misc. cleanup in analog section
    * added net-tie and dedicated return for headphone to avoid running over much of the DAC circuit
    * route SSG on back layer
    * ground fill on top
2021-03-21 sch: added rev. text
2021-03-21 pcb / sch: added CERL-OHL license
2021-03-21 rtl: fix S/PDIF left/right mixup
2021-03-24 sw / rtl: make pausing and unpausing sound sources a bit more robust
2021-03-24 doc: v1.0.1 testing note under TODO section
2021-03-27 fw / util: implement PCM block rearrangement and optimize
    This allows tracks with a 16MByte address space to work with only 8MB of PSRAM
2021-03-27 util: added YM2612 / PSG conversion
2021-03-27 doc: updated photo
2021-03-28 doc: improve the README
2021-03-28 pcb: tentative v1.0.1
2021-03-28 util: add gzip reader support and standalone converter
2021-03-28 doc: add /scripts README
2021-03-28 util: minor script corrections
2021-03-29 util: fix PCM block sorting for non-unified games
    ADPCM-A/B use separate address spaces in older tracks and this needs to be respected when PCM blocks are remapped
2021-03-29 doc: link to Genesis demo in README
2021-03-29 fw: USB control request refactor
2021-03-29 doc: better README summary
2021-04-01 util: fix various issues with VGM converter script
2021-04-01 util: removed PCM block merging which isn't needed anymore
    It also caused issues of its own
2021-04-05 1.0.0 of PCB as pictured in repo
2021-04-05 rtl: added ENABLE_MIDI parameter
    This should be 0 if the MIDI input components are populated or else the UART will have a floating input, possibly affecting software.
2021-04-07 doc: updated PCB photo and README
2021-04-08 util: minor script cleanup
2021-04-09 doc: README update
2021-04-10 misc: ignore transient debugging files
2021-08-29 rtl: minor cleanup with no functional change
2021-08-29 sw: fix looping issues on large tracks
2021-08-29 sw: fix more looping issues
2021-08-29 util: minor cleanup on USB polling (timeout handling)
2021-08-29 sw: add sequence counter to filter unexpected requests
2021-09-01 util: add YM2612 DAC conversion using ADPCM-B
2021-09-01 sw: minor cleanup, no functional change
2021-09-01 doc: added more context to README
2021-09-03 util: add requirements.txt for pyusb and README context
2021-09-03 doc: link to scripts README
2021-09-09 rtl: fix ADPCM-B reader glitches that affected a few chips
2021-09-24 pcb: v1.1.0
    * Layout cleanup and removal of now-redundant parts
    * Fixed lots of plane breakage near center of board
    * Added 47pF caps to RMPX/PMPX
    * Updated .pcf with reassigned pins
2021-09-26 sch: minor cleanup
2021-09-26 doc: add assembled PCB of v1.1.0
2021-09-26 doc: correct photo
2021-09-27 misc: remove unused files
